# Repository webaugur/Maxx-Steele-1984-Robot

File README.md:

# Maxx-Steele-1984-Robot

Information, code, and modifications for the 1984 Maxx Steele robot from Ideal (CBS Toys). This repository replaces the archive from the now-closed Yahoo Groups.

The intent is to allow people who own, repair, or modify their robots to share information. Feel free to request to fold your own additions back into the repository.

Much of the information in this archive has unknown ownership or uses licensed names and artwork. Everything here is believed to be appropriately used under Fair Use. If you are a copyright or trademark owner, please contact the maintainer so that appropriate use may be agreed upon.

## Naming conventions

| Scope | Rule | Examples |
|-------|------|----------|
| **Top-level hardware modules** | `CamelCase` (no spaces or hyphens) | `Transmitter/`, `Mainboard/`, `PaddleMirror/`, `Cartridge/` |
| **Top-level shared folders** | `lowercase` | `tools/`, `libraries/` |
| **Third-party datasheets** | **`DataSheets/`** (overrides lowercase rule) | Vendor PDFs as `OEM-PartNumber.pdf`; see [`DataSheets/README.md`](DataSheets/README.md) |
| **Community manuals** | **`Docs/`** + CamelCase subfolders | [`Docs/User/`](Docs/User/), [`Docs/Technical/`](Docs/Technical/), [`Docs/Mechanical/`](Docs/Mechanical/) |
| **Subfolders inside modules** | `CamelCase` | `Photos/`, `Firmware/`, `KiCAD/`, `PCBoard/`, `Model3D/`, `Photos/Product/`, `Photos/ReverseEngineering/` |
| **Subfolders inside shared folders** | `lowercase` | `tools/rfcap/`, `tools/rfcap/captures/` |
| **All filenames** | shell-safe: `[A-Za-z0-9._-]` only | `Remote-Front.jpg`, `maxx-song-1.wma`, `Maxx-Steele-Transmitter-Reverse-Engineered-Notes.pdf` |

Multi-word module or folder names run together (`PaddleMirror`, not `Paddle Mirror`). Acronyms keep familiar casing inside CamelCase (`KiCAD`, `PCBoard`).

**Filenames** must be shell-safe: only ASCII letters, digits, dot (`.`), underscore (`_`), and hyphen (`-`). No spaces or other punctuation. Use hyphens between words (`Remote-Front.jpg`, `maxx-song-1.wma`). Check or fix names with:

```bash
python3 tools/sanitize_filenames.py          # dry-run
python3 tools/sanitize_filenames.py --apply  # git mv fixes
```

## Repository layout

### Hardware modules

Each module has a [`KiCAD/`](Transmitter/KiCAD/) subfolder for schematic/PCB work and shares [`libraries/`](libraries/) for symbols.

| Module | Status | KiCad project |
|--------|--------|---------------|
| [`Transmitter/`](Transmitter/) | Active — [architecture](Transmitter/transmitter-architecture.md), [BOM](Transmitter/transmitter-bom.md) | [`Transmitter/KiCAD/Transmitter-27MHz.kicad_pro`](Transmitter/KiCAD/Transmitter-27MHz.kicad_pro) |
| [`Receiver/`](Receiver/) | Active | [`Receiver/KiCAD/Receiver-27MHz.kicad_pro`](Receiver/KiCAD/Receiver-27MHz.kicad_pro) |
| [`Power/`](Power/) | Planned | `Power/KiCAD/` |
| [`Mainboard/`](Mainboard/) | Planned | `Mainboard/KiCAD/` |
| [`Face/`](Face/) | Planned | `Face/KiCAD/` |
| [`Cartridge/`](Cartridge/) | ROM, firmware, [programming manual](Cartridge/PROGRAMMING.md), [technical manual](Docs/Technical/README.md) | [`CBSDemo.kicad_pro`](Cartridge/Examples/CBSDemo/KiCAD/CBSDemo.kicad_pro) (active); UltraMaxx planned |
| [`PaddleMirror/`](PaddleMirror/) | Archive | `PaddleMirror/KiCAD/` (planned) |
| [`Chassis/`](Chassis/) | Body, manuals, photos | `Chassis/KiCAD/` (mechanical, planned) |

### Documentation & tools

| Path | Description |
|------|-------------|
| [`Docs/`](Docs/) | Community manuals — [index](Docs/README.md) |
| [`Docs/User/`](Docs/User/) | Owner manual (setup, operation, games) — [PDF](Docs/User/Maxx-Steele-User-Manual.pdf) |
| [`Docs/Technical/`](Docs/Technical/) | Technical manual (bytecode, ROM, I/O) — [PDF](Docs/Technical/Maxx-Steele-Technical-Manual.pdf) |
| [`Docs/Mechanical/`](Docs/Mechanical/) | Mechanical manual (disassembly, photos) — [PDF](Docs/Mechanical/Maxx-Steele-Mechanical-Manual.pdf) |
| [`DataSheets/`](DataSheets/) | Third-party component datasheets (indexed in [`DataSheets/README.md`](DataSheets/README.md)) |
| [`tools/`](tools/) | [`tools/bin/`](tools/bin/) shell commands (`maxx`, `maxx-rom`, `picorom-cart`), [`maxxbas/`](tools/maxxbas/) Rust library + `maxx simulate`, Python modules, KiCad helpers, [`rfcap/`](tools/rfcap/) GNU Radio OOK flowgraphs |
| [`libraries/`](libraries/) | Shared KiCad symbol libraries |

## Paths

Scripts resolve **project-relative** paths from the repository root (`tools/project_paths.py`). KiCad modules use `${KIPRJMOD}/../../libraries/` for shared symbols.

## Quick commands

```bash
export PATH="$(pwd)/tools/bin:$PATH"

maxx compile Cartridge/Examples/UltraMaxx/Firmware/Basic/hello.bas
maxx list Cartridge/Examples/UltraMaxx/Firmware/Binary/hello.532 --json
maxx upload Cartridge/Examples/UltraMaxx/Firmware/Basic/hello.bas --device maxx_cart --dry-run
maxx simulate Cartridge/Examples/UltraMaxx/Firmware/Binary/hello.532 --gui

# KiCad 10: open Transmitter/KiCAD/Transmitter-27MHz.kicad_pro
```

See [`tools/bin/README.md`](tools/bin/README.md) for all commands.

## Related repositories

- [cop41xl-kicad-library](https://github.com/webaugur/cop41xl-kicad-library) — upstream COP400 KiCad symbols

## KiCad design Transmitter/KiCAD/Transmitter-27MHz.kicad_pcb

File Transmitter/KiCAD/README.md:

# Transmitter — KiCad 10

27 MHz remote transmitter schematic and PCB.

## Open in KiCad 10

**Open [`Transmitter-27MHz.kicad_pro`](Transmitter-27MHz.kicad_pro)** — not the legacy `.pro` / `.sch` pair (those expect a generated `*-cache.lib`).

| File | Description |
|------|-------------|
| [`Transmitter-27MHz.kicad_pro`](Transmitter-27MHz.kicad_pro) | KiCad 10 project |
| [`Transmitter-27MHz.kicad_sch`](Transmitter-27MHz.kicad_sch) | Native schematic (symbols embedded) |
| [`Transmitter-27MHz.kicad_pcb`](Transmitter-27MHz.kicad_pcb) | PCB layout (upgraded to KiCad 10 format) |
| [`Transmitter-27MHz-schematic.pdf`](Transmitter-27MHz-schematic.pdf) | Exported schematic PDF |
| [`Transmitter-27MHz.sch`](Transmitter-27MHz.sch) | Legacy schematic (kept for reference) |
| [`Transmitter-27MHz.pro`](Transmitter-27MHz.pro) | Legacy project (superseded) |

## Regenerate native files

```bash
python3 tools/upgrade_legacy_sch.py Transmitter/KiCAD/Transmitter-27MHz.sch
kicad-cli pcb upgrade Transmitter/KiCAD/Transmitter-27MHz.kicad_pcb
```

## ERC / DRC / netlist

```bash
kicad-cli sch erc Transmitter/KiCAD/Transmitter-27MHz.kicad_sch
kicad-cli pcb drc Transmitter/KiCAD/Transmitter-27MHz.kicad_pcb
kicad-cli sch export netlist Transmitter/KiCAD/Transmitter-27MHz.kicad_sch -o /tmp/Transmitter-27MHz.net
```

Netlist and BOM exports are regenerated on demand (not committed — see root `.gitignore`).

The upgraded schematic loads and runs ERC in KiCad 10. Remaining violations are from the original design (e.g. undriven nets, footprint filters) — resolve during schematic/PCB sync work.

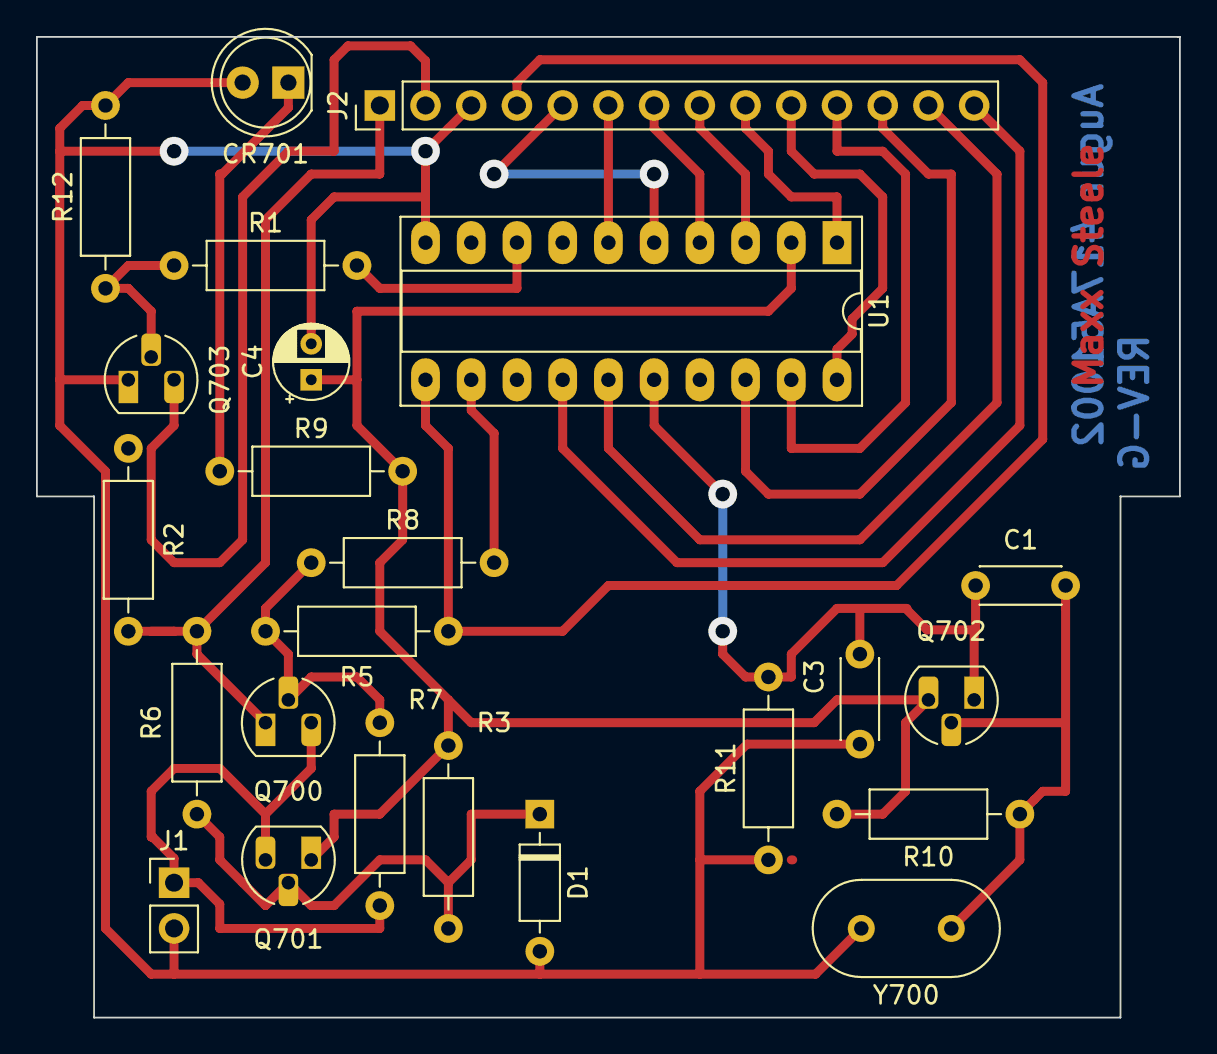
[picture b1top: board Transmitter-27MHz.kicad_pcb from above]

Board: 2 copper layers, 63.5 x 54.5 mm, 24 parts (0 on the bottom side), 24 nets.

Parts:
C1: .002µF; C_Disc_D4.3mm_W1.9mm_P5.00mm
C3: .001µF; C_Disc_D4.3mm_W1.9mm_P5.00mm
C4: 1.5µF; CP_Radial_D4.0mm_P2.00mm
CR701: LED; LED_D5.0mm
D1: 1N5232B; D_DO-35_SOD27_P7.62mm_Horizontal
J1: PRPC040SACN-RC; PinHeader_1x02_P2.54mm_Vertical
J2: PRPC040SACN-RC; PinHeader_1x14_P2.54mm_Vertical
Q700: S8550; TO-92_HandSolder
Q701, Q702, Q703: 2N3904; TO-92_HandSolder
R1: 4.7kΩ; R_Axial_DIN0207_L6.3mm_D2.5mm_P10.16mm_Horizontal
R2: 8.2kΩ; R_Axial_DIN0207_L6.3mm_D2.5mm_P10.16mm_Horizontal
R3: 10k; R_Axial_DIN0207_L6.3mm_D2.5mm_P10.16mm_Horizontal
R5: 3.9k; R_Axial_DIN0207_L6.3mm_D2.5mm_P10.16mm_Horizontal
R6: 220; R_Axial_DIN0207_L6.3mm_D2.5mm_P10.16mm_Horizontal
R7: 3.3k; R_Axial_DIN0207_L6.3mm_D2.5mm_P10.16mm_Horizontal
R8: 1K; R_Axial_DIN0207_L6.3mm_D2.5mm_P10.16mm_Horizontal
R9: 330; R_Axial_DIN0207_L6.3mm_D2.5mm_P10.16mm_Horizontal
R10: 33k; R_Axial_DIN0207_L6.3mm_D2.5mm_P10.16mm_Horizontal
R11: 1k; R_Axial_DIN0207_L6.3mm_D2.5mm_P10.16mm_Horizontal
R12: 2.7k; R_Axial_DIN0207_L6.3mm_D2.5mm_P10.16mm_Horizontal
U1: COP411; DIP-20_W7.62mm_Socket_LongPads
Y700: 455KHz; Resonator-2Pin_W10.0mm_H5.0mm

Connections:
/+5.6V: C4.1, Q701.1, Q702.3, R7.2, R9.2, R10.2, U1.2
/+9Vin: J1.1, Q700.3, Q701.3, R3.2
/+9Vout: J2.1, Q700.1, R2.1, R6.1
/CKI: C1.2, C3.1, Q702.1, R11.2, U1.16
/D0: J2.13, U1.15
/D1: J2.14, U1.14
/DataOut: J2.2, Q703.3, R2.2
/L0: J2.6, U1.6
/L1: J2.5, U1.5
/L2: J2.7, U1.4
/L3: J2.8, U1.3
/L4: J2.9, U1.1
/L5: J2.10, U1.20
/L6: J2.11, U1.19
/L7: J2.12, U1.18
/PD: R8.2, U1.12
/PK: J2.4, R5.2, U1.11
GND: C3.2, C4.2, CR701.2, D1.2, J1.2, J2.3, Q703.1, R11.1, R12.2, U1.10, Y700.2
unnamed: C1.1, Q702.2, R10.1, Y700.1
unnamed: CR701.1, R9.1
unnamed: D1.1, Q701.2, R6.2, R7.1
unnamed: Q700.2, R3.1, R5.1, R8.1
unnamed: Q703.2, R1.1, R12.1
unnamed: R1.2, U1.8

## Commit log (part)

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2026-06-23 Add reverse-engineering docs, firmware tools, and KiCad library integration.
    - Cartridge programming manual and ROM analysis tooling
    - COP411L KiCad library wired into transmitter/receiver projects
    - Transmitter BOM, references, and schematic assets
    - Exclude large GNU Radio IQ capture .dat files from version control
2026-06-23 Reorganize KiCad projects under Transmitter/ and Receiver/.
    - Move transmitter project to Transmitter/KiCAD/
    - Move receiver schematic to Receiver/KiCAD/
    - Relocate shared cop41xl library to libraries/ at repo root
    - Update docs and sym-lib-table paths; remove top-level KiCAD/
2026-06-24 Move schematic and PCB reference images to docs/Photos.
    Relocate sch/ contents (trace overlays, PCB photo, handwritten BOM)
    and update README and doc cross-references.
2026-06-24 Add project-root path resolution; remove remaining hardcoded paths.
    Introduce tools/project_paths.py for repo-relative paths. Wire maxx_rom
    and RemoteSpectrum to use it; document KiCad ${KIPRJMOD} conventions.
2026-06-24 Reorganize by hardware module with KiCAD subfolders.
    Move projects to Transmitter/KiCAD and Receiver/KiCAD; restore shared
    libraries/ at repo root. Add Power, Mainboard, and Face module placeholders
    with KiCAD/ and sym-lib-table wiring.
2026-06-24 Add Chassis and Mainboard READMEs; update doc cross-references.
    Follow-up to Chassis folder creation — module docs and path updates.
2026-06-24 Move rfcap under tools/
    Relocate GNU Radio flowgraphs and capture docs to tools/rfcap/,
    update project_paths, RemoteSpectrum.py imports, and doc links.
    Legacy rfcap/captures/ paths still resolve for old recfile values.
2026-06-24 Replace null.txt placeholders with README backlog links
    Empty schematic, PCB, and 3D folders now explain their status
    and link to the matching TODO.md section.
2026-06-24 Rename Demo Cartridge module to Cartridge
    Update paths and cross-references across READMEs, docs, and TODO.md.
2026-06-24 Document GitHub Issues workflow for TODO tracking
    Issues are disabled on the repo today; add setup table and sync
    instructions when enabling Settings → Features → Issues.
2026-06-24 Consolidate third-party datasheets under DataSheets/
    Override naming rule: top-level DataSheets/ for all vendor PDFs
    with indexed README linking related modules and docs. Module
    Datasheets/ folders become pointers; remove duplicate COP411L.pdf
    from docs/references/.
2026-06-24 Move DataSheets archival notice to footer in small text
2026-06-24 Remove docs/references; canonical copy is under Transmitter
    The RE notes PDF was a byte-identical duplicate of
    Transmitter/ReverseEngineering/. Point docs and README links at the module
    copy and drop the redundant docs/references/ folder.
2026-06-24 Fold module Datasheets READMEs into module READMEs
    Move transmitter and chassis datasheet pointers into a Datasheets section
    on each module README and remove the redundant Datasheets/ subfolders.
2026-06-24 Add auto-built Programmers Guide PDF for GitHub files section
    Merge ProgrammersGuide chapters with tools/build_programmers_guide_pdf.py
    and publish Maxx-Steele-Programmers-Reference.pdf in the repo.
2026-06-24 Update Programmers Guide PDF [skip ci]
2026-06-24 Add Technical Manual PDF workflow with cover page support
2026-06-24 Use full-bleed fill for technical manual cover pages
    Switch img2pdf from shrink to fill so front/rear covers scale to cover
    the entire Letter page without letterboxing whitespace.
2026-06-24 Format technical manual as 8.5x6.5 inch booklet pages
    Set pandoc body and cover pipeline to 8.5in x 6.5in (612x468pt) so
    covers match interior page size. Use 0.5in margins and 10pt type on the
    smaller trim; keep shrink-fit covers with horizontal edge extension.
2026-06-24 Keep headings with following content in technical manual PDF
    Add needspace guards before section, subsection, and subsubsection
    headings so LaTeX inserts a page break when a heading would otherwise
    sit alone at the bottom of a page.
2026-06-24 Document remote faceplate button names from product photo
    Add Transmitter/remote-keypad.md and Remote-Front.svg with matrix keys
    A–Y mapped to faceplate labels from Remote-Front.jpg. Update cartridge
    manual, technical manual I/O chapter, and Transmitter READMEs.
2026-06-24 Use internal PDF navigation for technical manual links
    Map same-guide .md cross-references to Pandoc section anchors so chapter,
    appendix, and TOC links jump within the PDF. Strip external HTTP and file
    links (including the self-referential PDF link) to plain text.
2026-06-24 Restore full-bleed img2pdf covers in technical manual PDF
    Embed img2pdf cover pages via pdfpages within the single LaTeX build so
    cover rendering matches the original pipeline while TOC and internal
    links stay correct.
2026-06-24 Add CBSDemo cartridge partial schematic (rev 0.1)
    Reverse-engineer the factory demo cart from maxxcard.jpg and the Model3D
    STEP assembly: KiCad schematic, PDF, BOM, trace worksheet, and reference
    photo crops. J1 is a 44-position 2.54 mm card edge per STEP; U1 27C512,
    U3 5085-TBD, U2 glue logic placeholder. Includes gen_cartridge_sch.py and
    doc updates for Cartridge, UltraMaxx, DataSheets, and TODO.
2026-06-24 Upgrade legacy KiCad schematics to KiCad 10 native format
    - Add tools/upgrade_legacy_sch.py to convert EESchema v4 .sch to .kicad_sch + .kicad_pro
    - Upgrade Transmitter and Receiver projects with embedded symbols and exported PDFs
    - Upgrade Transmitter PCB to KiCad 10 format via kicad-cli pcb upgrade
    - Add cop41xl.kicad_sym (upgraded from legacy cop41xl.lib) and update all sym-lib-table entries
    - Document KiCad 10 open instructions in Transmitter/KiCAD and Receiver/KiCAD READMEs
2026-06-24 Add UltraMaxx PicoROM adaptation based on CBSDemo hardware
    - Document PicoROM P28 drop-in for U1 in UltraMaxx/PICOROM.md
    - Add tools/picorom_cart.py to validate and upload .532 images via picorom CLI
    - Add Firmware/Makefile with validate/upload targets
    - Update PROGRAMMING.md, BOM, READMEs, and TODO for PicoROM workflow
2026-06-24 Unify Maxx toolchain under maxx CLI with simulator-ready ROM decode
    Add tools/maxx dispatcher wrapping the Rust maxx binary with compile,
    check, validate, list (--json ProgramTrace), upload, and simulate commands.
    Wire picorom_cart.py to compile .bas/.maxx via maxx upload. Export typed
    StepKind JSON from maxxbas for a future vector-graphics robot simulator.
2026-06-24 Translate CBS Demo ROM to MaxxBAS cbsdemo.bas
    Add full 38-step factory program as MaxxBAS source with ARMS, WRIST,
    and CLAW statements. Compiler gains --tables-from to copy phrase/music
    tables from CBSDemo.532; compiled output is byte-identical to factory ROM.
2026-06-25 Add unified simulator, cross_street example, and manual link fixes
    Introduce `maxx simulate` with ASCII storyboard, optional egui GUI
    (`--gui`), and patched 65C02 firmware boot. Add Simulator/ docs and
    patches, cross_street.bas example, and integration tests.
    Technical manual: hyperlink repo file references, remove redundant
    §1.4 table of contents, and add tools/check_manual_links.py verifier.
2026-06-25 Add mechanical manual, chassis photo index, and hardware assets CSV
    Introduce MechanicalManual from Mike McCarty disassembly guide with
    disassembly/reassembly chapters, full chassis photo reference (Ch 3),
    and rebuilt PDF with embedded images.
    Move teardown photos to Chassis/Photos/Disassembly; remove duplicate
    Copy-of-IMG exports from Chassis/Disassembly.
    Add Hardware-Assets.csv (164 rows) and generator scripts for chassis
2026-06-25 Trigger technical manual PDF rebuild when manual_pdf.py changes
2026-06-25 Move internal ROM firmware from Chassis/ to Mainboard/
    Relocate masked 6502 ROM binary and disassembly to Mainboard/Firmware/
    where it belongs with the main logic board. Update Technical Manual,
    PROGRAMMING.md, simulator embed path, Hardware-Assets.csv, and README
    cross-links.
2026-06-25 Add MMIO pin map, IC inventory, and Ch 6 bitfields
    Document mainboard/face IC inventory with confidence tiers, partial
    MMIO pin-mapping schematic (decode $1000-$1E00), and auto-generated
    ROM cross-reference (tools/gen_mmio_crossref.py). Expand Technical
    Manual Ch 6 with MMIO bitfield tables; add Appendix M; update
    DataSheets refdes notes and rebuild PDF.
2026-06-25 Add User Manual PDF GitHub Actions workflow
2026-06-25 Make User Manual markdown the source of truth; bootstrap from PDF optional
    gen_user_manual_chapters.py no longer overwrites chapters by default.
    Add bootstrap_user_manual_from_pdf.py for explicit OCR re-seed. Update
    UserManual README; CI workflow path filters updated separately.
2026-06-27 Move community manuals under Docs/{User,Technical,Mechanical}
    Consolidate UserManual, TechnicalManual, and MechanicalManual into a
    scalable Docs/ layout. Centralize paths in tools/manual_paths.py, update
    cross-links, regenerate Hardware-Assets.csv and chassis photo chapter with
    short User|Technical|Mechanical tags.
2026-06-27 Update Mechanical Manual PDF [skip ci]
2026-06-27 Add live MaxxOS simulator GUI (maxx 0.2.22)
    Introduce InteractiveFirmware with heap-stable LiveBus keypad injection,
    remote panel GUI, CPU trace, and 59 regression tests. Fixes LDX $75
    reading stale wire bytes after InteractiveFirmware moves into the egui
    app (Box<LiveBusState>).
    Includes MaxxOS example cart, launcher version reporting, and rebuilt
    tools/bin/maxx.
2026-06-27 fix(sim): sticky latched_digit + immediate GUI keypress (0.2.24)
    - Wire effective_pending_key() through step() injection/bypass paths so
    latched_digit survives premature pending_digit clears
    - digest_keypress runs CPU even when paused; trace shows latched=
    - Apply remote keys immediately in ui() instead of queuing to logic()
    - Add test for latched_digit bypass at $E6AC without pending_digit
2026-06-27 fix(sim): remote clicks were never reaching press_key (0.2.27)
    Trace showed pending=-- latched=--: GUI clicks did not register. Use
    egui::Button for remote keys, apply press_key immediately on click,
    add keyboard 0-9 fallback, and show keys= counter in toolbar. Clarify
    that LED [6?] is the ROM quiz prompt, not proof of input.
2026-06-27 release(sim): live GUI keypad injection v0.2.33
    Fix MaxxOS toolbar/remote digit delivery in the live simulator after
    clicks reached press_key but ROM poll at $E617 never saw the key.
    Sim (0.2.29–0.2.33):
    - Deep stack unwind through nested $E959/$E6A4 JSR frames to cart $A199
    - Sticky gui_digit + gui_armed latch survives cart re-poll at $E196
    - Synchronous keypress digest at 16k cycles/frame after toolbar delivery
2026-06-28 release(sim): live GUI polish, remote skin, toolbar controls v0.2.37
    - Dual plastic skin (remote grey shell + #111 window chrome)
    - Remote branding: status LEDs, MAXX logo, fixed-width transmitter panel
    - Toolbar: IEC transport keys, step insn/frame (halt-only), speed slider
    - Boot gate fix for auto-start after window paint
    - Python subprocess interrupt handling (process_util)
    - Speech/display font assets; resvg for logo rasterization
2026-06-29 release(sim): trace column layout and rebuild preflight v0.2.42
    Move execution and trace toolbars into the center column only, with fixed
    333px rects matching the remote panel. Split status and transport rows so
    controls fit without clipping, and size the trace TextEdit to the full column
    width. Add ensure_maxx_built preflight and auto-rebuild when maxxbas sources
    change.
